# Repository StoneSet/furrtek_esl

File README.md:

# ESL EMITTER HACK - V1 of 2014

### The Eagle project of the esl project + apk and hex files

**(c) Found the entire project here (not the v1 but u can found it on the web archive): http://furrtek.free.fr/?a=esl**

### TO DO

- Web version of the app (Capability to change page)
- Decompile the app ✅ (Now we will spend many hours to understand the code...)

## Included :

- All needed files to modify the project
- BOM (in /pcb/)
- Prog files & source (not commented) for the APK (in /android/apk/)

## To use it :

1. Buy the pcb then solder every composants.
2. Flash the Attiny85 with phxtx1.hex with these fuses :

- Low: *0xEF*, High: *0xDD*, Extended: *0xFF*

4. Install [pricehax15.apk](https://github.com/StoneSet/furrtek_esl/blob/master/apk/pricehax15.apk  "pricehax15.apk") on your phone (only Android at this time)
5. Plug the jack cable in your phone, launch the app and vouala !

## Some img's :

------

### To dot it, you will need :

| Components | list |
|--|--|
| x1 Attiny85 | x1 78L05 regulator |
| x2 100µF capacitor | x1 10nF ceramic capacitor |
| x2 22pF ceramic capacitor | x1 3.3nF ceramic capacitor |
| x1 10k resistor | x1 100k resistor |
| x1 3.3k resistor | x1 10MHz quartz |
| x1 220ohm resistor | x1 47ohm resistor |
| x1 SFH485P IR LED - 880NM | x1 9v battery clip |
| x1 2N2222 transistor | x1 SPDT Switch |
| x1 A randomly chosen diode |

This version work finely !

#

(c) @furrtek & @StoneSet & @lefuturiste - http://furrtek.free.fr/?a=esl - http://stoneset.github.io/ (2019)

*Prog infos etc here* : [https://github.com/Jonas1312/Pricehax](https://github.com/Jonas1312/Pricehax)

plz do not steal, i'm not the owner of this project, i'm only the owner of this pcb. Have fun !

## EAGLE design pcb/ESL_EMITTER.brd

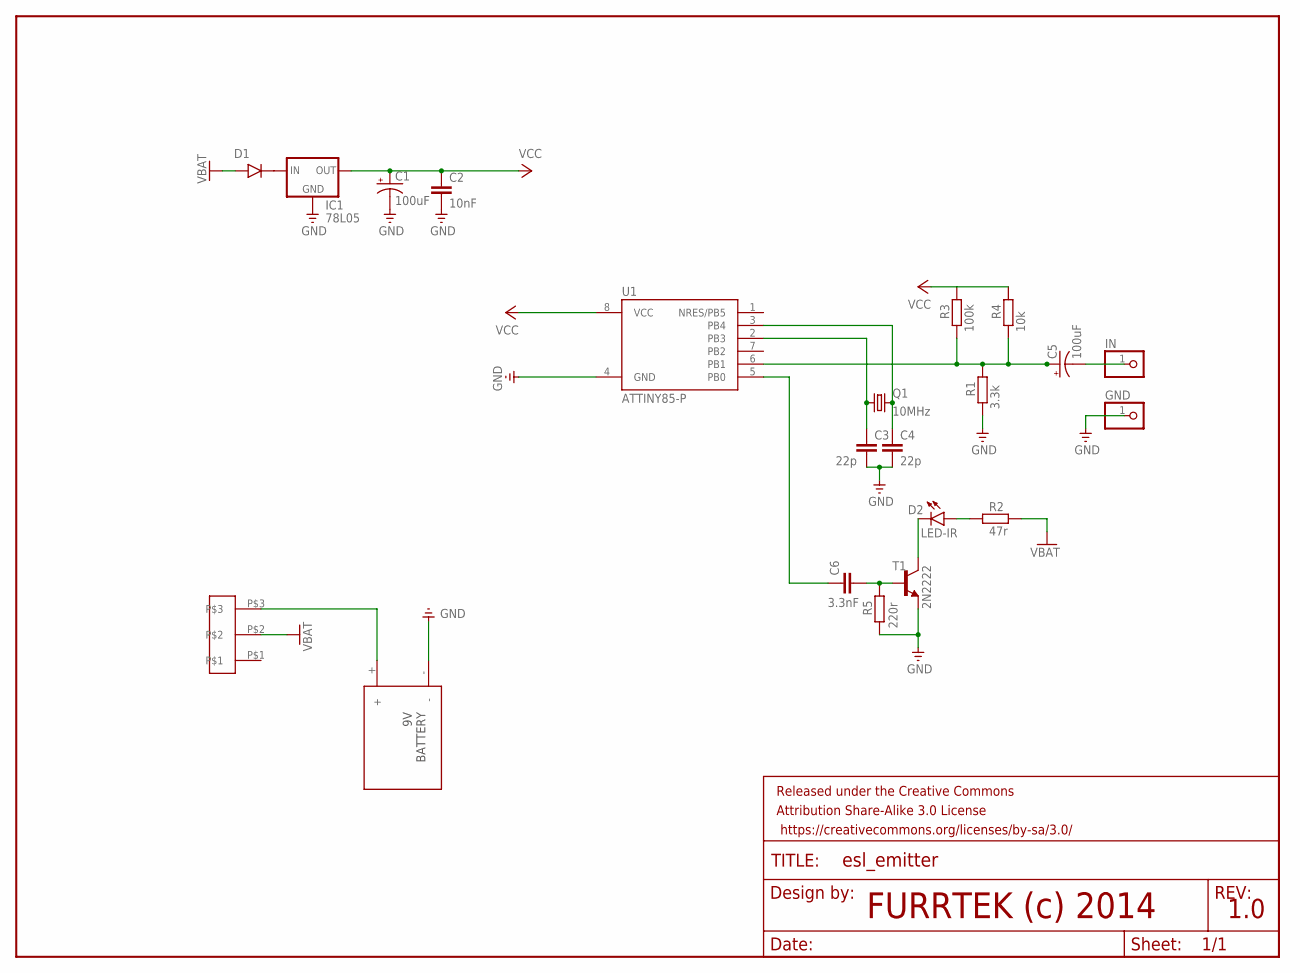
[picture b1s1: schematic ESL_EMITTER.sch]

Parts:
C1, C5: 100uF; CPOL-RADIAL-10UF-25V
C2: 10nF; CAP-PTH-10MM
C3, C4: 22p; CAP-PTH-10MM
C6: 3.3nF; CAP-PTH-10MM
D1: 1N4001; DO41-10
D2: LED-IR; LED_3MM-NS
FRAME1: FRAME-LETTER; CREATIVE_COMMONS
GND: PINHD-1X1; 1X01
IC1: 78L05; 78XXL
IN: PINHD-1X1; 1X01
Q1: 10MHz; HC49U-H
R1: 3.3k; 0207/7
R2: 47r; 0207/7
R3: 100k; 0207/7
R4: 10k; 0207/7
R5: 220r; 0207/7
T1: 2N2222; TO92-EBC-OVAL
U1: ATTINY85-P; PDIP08_300MIL
U$2: PACKAGESWITCH; SLIDESWITCH
U$3: BAT

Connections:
GND: C1.2 (-), C2.2, C3.2, C4.2, GND.1, IC1.GND, R1.1, R5.1, T1.E, U1.4 (GND), U$3.-
unnamed: D1.C (CATHODE), IC1.IN
unnamed: C4.1, Q1.2, U1.3 (PB4)
unnamed: C3.1, Q1.1, U1.2 (PB3)
unnamed: C5.1 (+), R1.2, R3.1, R4.1, U1.6 (PB1)
unnamed: C6.2, R5.2, T1.B
unnamed: C6.1, U1.5 (PB0)
unnamed: D2.K (C), T1.C
unnamed: C5.2 (-), IN.1
unnamed: U$2.P$3, U$3.+
unnamed: D2.A, R2.1
VBAT: D1.A (ANODE), R2.2, U$2.P$2
VCC: C1.1 (+), C2.1, IC1.OUT, R3.2, R4.2, U1.8 (VCC)

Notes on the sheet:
FURRTEK (c) 2014
1.0

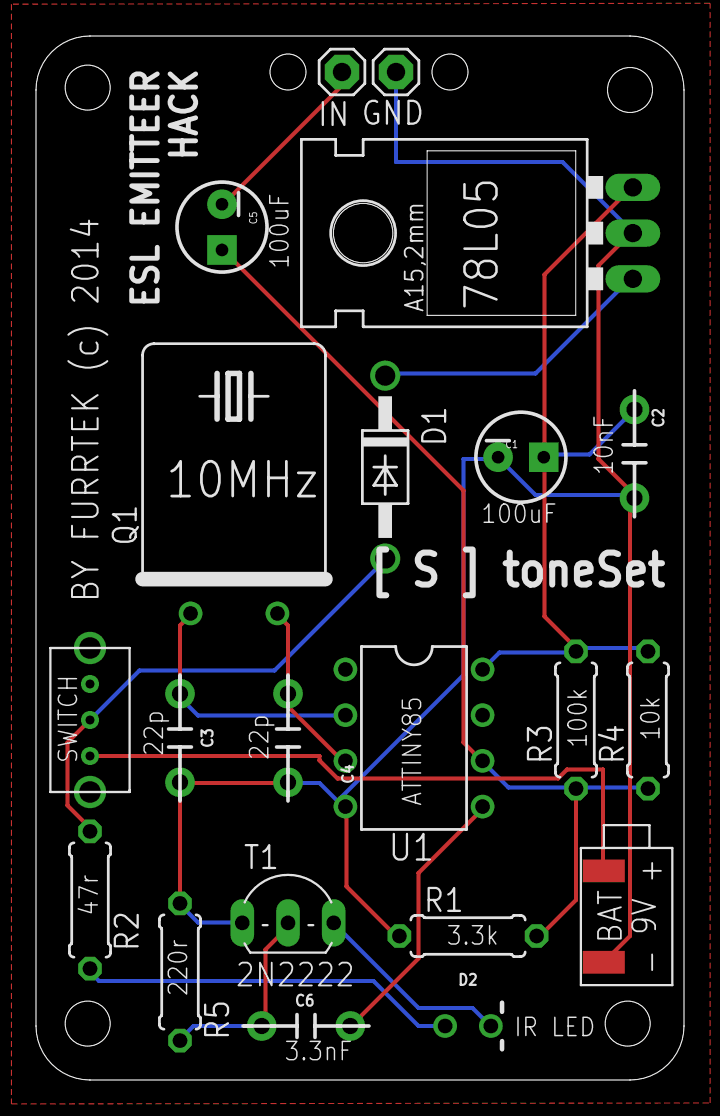
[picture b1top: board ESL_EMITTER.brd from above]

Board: 2 copper layers, 36.0 x 58.0 mm, 22 parts (0 on the bottom side), 13 nets.

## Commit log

2019-06-12 feat(labels): add labels & some fix
2019-06-12 fix: wrong img (board&schematics)
2019-06-12 fix: capacitor&bom : last release
2019-06-12 fix: iam idiot
2019-07-19 feat(img): add more descriptive pictures
2019-07-19 feat(img): add more descriptives pictures
2019-07-21 feat(infos): add bom, update imgs etc
2019-07-21 fix(img): idiot man
2019-08-06 feat: add pricehax android app source code
2019-08-06 feat(refactor): refactor the repo & the readme
2019-08-06 fix(idiot): idiotman
2019-08-08 [WIP] feat(web): test
2019-08-08 feat(web): new readme

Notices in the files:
pcb/ESL_EMITTER.brd:
BY FURRTEK (c) 2014
parts and their libraries:
SparkFun-Capacitors: Licensing: Creative Commons ShareAlike 4.0 International - https://creativecommons.org/licenses/by-sa/4.0
supply0: Copyright (C) 2007, Bob Starr
SparkFun-Retired: Released under the Creative Commons
SparkFun-Retired: https://creativecommons.org/licenses/by-sa/3.0
